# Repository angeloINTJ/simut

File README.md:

<p align="center">
  <picture>
    <source media="(prefers-color-scheme: dark)" srcset="docs/images/logo-wordmark-dark.svg">
    <source media="(prefers-color-scheme: light)" srcset="docs/images/logo-wordmark.svg">
    
  </picture>
</p>

# SIMUT — Sistema Integrado de Monitoramento Universal e Telemetria

> In English, *Integrated Universal Monitoring and Telemetry System*. The name is Portuguese, and so is the acronym: it is not translated.

> Offline-first monitoring and telemetry for the Raspberry Pi Pico W and Pico 2 W, on sixteen universal sensor slots

[English](README.md) | [Português](README.pt-BR.md) | [Español](README.es-ES.md)

## Overview

SIMUT is monitoring and telemetry firmware for the **Raspberry Pi Pico W** and the **Pico 2 W**. It reads up to 16 sensors on universal slots — temperature, humidity and pressure today, through its DS18B20, DHT22 and BMP280/BME280 drivers — records them on the device, raises alarms, and keeps working with or without a network. One source tree builds three published devices:

- a **touch-panel monitor** (320×240 TFT);
- a **character-LCD monitor** (16×2, the *alpha*);
- a **battery logger** that hibernates between readings (the *Air*, experimental).

They share one core:
- binary on-device history and per-channel alarms;
- 32 user accounts with 13 permission bits;
- an embedded web interface;
- telemetry over HTTP(S) or MQTT(S), with a separate line for alarms;
- Home Assistant MQTT Discovery, a Prometheus `/metrics` endpoint and remote syslog (RFC 5424);
- over-the-air updates and a serial console.

**Universal is the direction, not a feature.** A slot has no fixed quantity: a sensor type is a driver under `src/sensors/` and an entry in the type table, a new quantity is a row in the channel table (four of the eight it has room for are used), and the dashboard, the history, the alarms, the calibration and the telemetry read the driver's metadata instead of special-casing a part ([adding a sensor](docs/adding-a-new-sensor.md)). Three drivers ship today, and the table already has a row for luminosity that none of them fills. The project's direction is more drivers, contributed one at a time, and slots that actuate — relays, valves, signals — as well as read. No image drives an output yet: an alarm is a sound, a screen and a message to your server.

## Project status

| | |
|---|---|
| **Current release** | **v2.14.0** (2026-11-05); the [changelog](CHANGELOG.md) says what each version changed. SIMUT left beta with v2.7.0, on measurements: an 8.18 h soak with 0 reboots, and 6 of 6 over-the-air updates with nothing lost. |
| **Published images** | Four images, each as `.uf2` and `.bin`. For the Pico W: `release` (TFT touch panel), `alpha` (16×2 LCD with a Bluetooth console) and `air` (headless battery logger). For the Pico 2 W (RP2350): `releasetwo`, the release, whose `.uf2` carries its partition table and whose `.bin` boots on trial. The pt-BR and es-ES language packs and an OTA manifest ship alongside. An image with a different set of features comes from the [build configurator](https://angelointj.github.io/simut/configurador/), and CI builds it from `main`, for the Pico 2 W too. |
| **Maturity** | <ul><li>`release`: **stable**.</li><li>`alpha`: published and bench-tested, its 16×2 LCD included since 2026-09-26.</li><li>`air`: **experimental**. Its one long soak failed: a sleep in cycle 119 never woke (F28). A watchdog across the wake now mitigates it; the root cause is not confirmed.</li><li>`releasetwo`: **new** in v2.11.0, bench-tested on one Pico 2 W (RP2350 A2). It updates over the air into its other slot, on trial, and goes back by itself when the update does not keep itself.</li></ul> |
| **Tests** | Every pull request runs 883 host test cases in 11 suites, 60 s of fuzzing and static analysis, and builds all eleven firmware images from a cold cache. Behaviour on real hardware is verified on a bench — see [Verification on hardware](docs/VERIFICATION.md). |

**Known limitations.** Each one is documented where it applies.
- **Updates.** On the Pico W, an update over the air reformats the filesystem:
  - Wi-Fi, accounts and sensor slots are carried across. History, calibration files and language packs are not, so the web page downloads a backup before it starts, and restoring it brings them back.
  - On the Pico W there is one firmware slot and no rollback. A bad flash is recovered with BOOTSEL and a USB cable. The Pico 2 W has two slots: an update goes into the other slot, leaves the filesystem alone and boots on trial, and the image it replaced comes back by itself if the new one does not keep itself ([What an update destroys](docs/MANUAL.md#what-an-update-destroys), [Rollback](docs/MANUAL.md#rollback)).
  - Since v2.9.0, only an image the project signed installs over the air: a release `.bin`, or a build from the configurator. A build of your own goes over USB.
- **Unexplained resets.** A watchdog reset (`ctx=209` or `ctx=455`) appeared three times on the test image on 20–21 September and not since; the one caught with its context had Core 0 in the console (`ctx=209`). Both cores are now instrumented to explain the next one. A `ctx=455` (empty trace) on the first boot after `picotool load -x` is not this: that reboot goes through the watchdog, and the record appeared after 11 of 11 such flashes and after none of 7 hardware resets (2026-09-30).
- **Idle connections.** During the v2.7.0 soak, 7.1 % of responses on an idle keep-alive connection arrived cut short. The device drops a stream it cannot send for 4 s.
- **Chunked replies.** Read in a tight loop, 0.15–0.6 % of `/api/status` replies arrive with their chunked framing broken ([#189](https://github.com/angeloINTJ/simut/issues/189)). The device does not restart and the next request works; the page misses one update.
- **Not a certified instrument.** SIMUT is not a certified metrological instrument. Validate it against your own reference before relying on it for regulated storage.

## Why SIMUT?

| Need | DIY Arduino sketch | ESPHome / Tasmota | **SIMUT** |
|------|:---:|:---:|:---:|
| Standalone with display | Manual coding | No TFT support | Built-in touch UI, or a 16×2 LCD |
| Regulated environments | No audit trail | No user RBAC | 32 accounts, per-account panel PIN, a persistent event log and remote syslog |
| Cold chain (probes down to −50 °C) | Basic readings | Basic monitoring | Calibrated multi-sensor, maintenance windows |
| Offline operation | Yes | Often cloud-dependent | Full local web + display |
| OTA updates | Manual reflash | OTA | Signed OTA + backup/restore |
| Security | None | Basic | HMAC-SHA256, 13-bit RBAC, lockouts, optional HTTPS |
| Home Assistant | Manual setup | Native | MQTT Discovery (opt-in) |
| Prometheus metrics | None | Built-in | `/metrics` endpoint |
| Remote audit log | None | Add-on | Syslog (RFC 5424 / UDP) |

**SIMUT is for you if:** you need a standalone, secure, auditable monitoring system that works with or without internet — today typical in laboratories, pharmacies, blood banks, vaccine storage and food cold chains, and wherever a sensor with a driver needs a screen, a history and an alarm.

**ESPHome/Tasmota may be better if:** you don't need a local display and prefer YAML configuration over a built-in web UI. (If what kept you there was Home Assistant: SIMUT speaks MQTT Discovery.)

## Architecture

<picture>
  <source media="(prefers-color-scheme: dark)" srcset="docs/images/architecture-dark.svg">
  <source media="(prefers-color-scheme: light)" srcset="docs/images/architecture.svg">
  
</picture>

Core 0 runs everything but the display, in one cooperative loop, and is the only core that writes the flash; Core 1 runs only the display, the touch panel or the LCD. The rules between the two are in [docs/CONCURRENCY.md](docs/CONCURRENCY.md). The figure is drawn from the source by `tools/readme_diagram.py`, and CI checks that it still matches the code.

## Screenshots

| TFT dashboard (Pico W) | TFT history graph (Pico W) | Web dashboard | Early alpha |
|:---:|:---:|:---:|:---:|
|  |  |  |  |

> Every screen of the Pico W's original panel, captured off the real panel framebuffer: [docs/images/screens/screens.md](docs/images/screens/screens.md).
>
> The **early alpha** video shows the first TFT + touch prototype — the UI has been redesigned since.

## Hardware

| Component | Specification |
|-----------|---------------|
| MCU | Raspberry Pi Pico W (RP2040) or Pico 2 W (RP2350), both dual-core. The SIMUT Wire, a plain Pico with an ENC28J60 Ethernet module in place of the radio (`pico_wire`, `pico_wiretft`), is built by CI and runs on the bench; it is not published |
| Display | `release`: ILI9341 320×240 TFT (SPI, DMA-driven), in the Ângulo look on the Pico 2 W (v2.12.0 and earlier drew the original panel there) and the original look on the Pico W · `alpha`: HD44780 16×2 character LCD (4-bit) · `air`: none |
| Touch | XPT2046 resistive touchscreen (`release`) |
| Sensors | **16 universal slots on GP0–GP15** — any mix of DS18B20 (1-Wire), DHT22 and BMP280/BME280. A BMx280 is I²C and takes two pins; two of them can share a pair (0x76/0x77). A new sensor type is a driver; a new quantity, a row in the channel table ([adding a sensor](docs/adding-a-new-sensor.md)) |
| Buzzer | Passive piezo (PIO-driven) — not on the Air |
| Storage | 2 MB internal flash (1 MB firmware slot + 1 MB LittleFS) |

See the **[wiring guide](docs/WIRING.md)** for the complete pinout and connection diagrams.

> **SIMUT PCB — layout available for download** — the KiCad board design (`.kicad_pcb`, `.kicad_sch`) lives in [`PCB_test/`](PCB_test/), and the ready-to-fab package (Gerbers + PTH/NPTH drills, no paste layers) is published as a public release: **[simut-pcb-v1.1 — `simut_pcb_fabrication.zip`](https://github.com/angeloINTJ/simut/releases/tag/simut-pcb-v1.1)**.

## Features

- **Sensing and alarms** — 16 universal sensor slots assigned at runtime, three drivers today (DS18B20, DHT22, BMP280/BME280) in a channel table open to more, calibration curves, per-channel limits, a fault alarm and maintenance windows.
- **Touch panel** (`release`) — dashboard, history graphs and calendar, and identity at the glass: an account, then its PIN. The Pico 2 W release draws it in the Ângulo look; the Pico W release keeps the original panel. v2.12.0 and earlier drew the original panel on the Pico 2 W.
- **Character LCD** (`alpha`) — every slot in turn, the setup access point and a Bluetooth console; since v2.14.0 the web dashboard draws the glass itself, captured once or live (`GET /api/lcd`).
- **Web interface** — 11 pages, a live panel mirror, history graphs and CSV export in the browser.
- **HTTP API** — 63 routes. Each one is either gated by a permission or public by design, and CI checks it. The images with the Ângulo panel add `GET /api/ui`, gated.
- **Telemetry** — HTTP, HTTPS, MQTT and MQTTS, batched by quantity, and a second, acknowledged line for alarms; Home Assistant, Prometheus and syslog.
- **Network and time** — Wi-Fi that reconnects itself, a setup access point opened on request, and NTP with a provisional clock until it syncs.
- **Storage** — the V5 binary history (about 116 days in 1 MB), a configuration with CRC32 and a `.bak`, and an event log with 170 event codes.
- **Security** — 32 accounts, 13 permission bits, salted HMAC-SHA256, lockouts and optional HTTPS.
- **Updates** — signed over-the-air updates from the web page, and backup and restore of the whole filesystem.
- **SIMUT Air** (experimental) — a battery logger that hibernates between readings.
- **Languages** — English built in; pt-BR and es-ES as language packs.

Every feature in detail, and which ones a custom build can leave out: **[docs/FEATURES.md](docs/FEATURES.md)**.

## Quick start

### Prerequisites
- [PlatformIO](https://platformio.org/) (Core 6.x or later)
- `pip install zopfli` — optional; the web pages compress 2,888 B smaller with it, and the flash budgets are measured with it
- Raspberry Pi Pico W
- No local toolchain? `docker compose run build` builds in a container — the path [CONTRIBUTING.md](CONTRIBUTING.md) recommends for new contributors

### Build and flash

```bash
# Clone the repository
git clone https://github.com/angeloINTJ/simut.git
cd simut

# Build firmware
pio run -e pico_w_release

# Flash to Pico W (auto-reset via 1200 bps touch; BOOTSEL works too)
pio run -e pico_w_release -t upload

# First flash only: upload LittleFS data (language packs, themes, favicon).
# Warning: uploadfs reformats the LittleFS partition — on a device already in
# service it destroys history, config and calibration. Never run it again
# after the device has data; language packs can be uploaded later from the
# web file manager instead. It copies both language packs, and the device
# loads the first alphabetically (es-ES): delete the one you do not want.
pio run -e pico_w_release -t uploadfs
```

Prefer not to build? Every [release](https://github.com/angeloINTJ/simut/releases/latest) ships `simut_vX.Y.Z_release.uf2`, `_alpha.uf2` and `_air.uf2` for the Pico W and, since v2.11.0, `_releasetwo.uf2` for the Pico 2 W (drag-and-drop with BOOTSEL held), the matching `.bin` for over-the-air updates, and the pt-BR and es-ES language packs. An image with a different set of features comes from the [build configurator](https://angelointj.github.io/simut/configurador/).

### First boot
1. **Capture the admin password.** A factory-fresh unit prints a random 8-character admin password **once on the USB serial console** (115200 baud). It is never stored in plain text. If you miss it, `system admin reset confirm` over USB prints a new one.
2. **Join it to your network.** The setup access point opens when you ask for it: type `ap` on the console (on the Air, after `enable`), or use Settings → 8 on the touch panel. From v2.7.1 to v2.8.0, a unit with no network configured opened it by itself; it no longer does.
   - Join `<name>_SETUP` (`simut_SETUP` from the factory). It is WPA2, and its per-device key is in the reply to `ap`, on the USB console and on the TFT's boot terminal.
   - The portal opens at `http://192.168.4.1`.
   - The device keeps measuring while the access point is up; only telemetry and syslog wait for the network. v2.7.1 to v2.8.0 read no sensors, checked no alarms and recorded no history while it was up.

   Without a screen, you can use the console instead: `system ssid <name>`, `system pass <secret>`, then `reload confirm`. The console stops at the first space, so a network name or password with a space has to go through the web page.

   With no network configured, the unit asks for the date and time at the end of the boot, because without a network there is no NTP: the touch panel opens a date-and-time screen (**SKIP** leaves it, and Settings → 4 sets the clock later), and every image prints `No network, provisional clock: conf time YYYY-MM-DD HH:MM:SS` on the console. That command works on every image's console, over USB or Bluetooth: on the alpha and the Air, which have no panel, it is how the question is answered. The web page's **Date & Time** section sets the clock too.
3. **Open the web interface** at the address the device got — on the `release` image also `http://simut.local` — and log in as `admin` with the password from step 1. You will be asked to choose a new one.
4. **Add sensors** in **Config → Sensors & GPIO**, or let *Scan for probes* find them.
5. **On the touch panel**, Settings asks for an account and its PIN. The factory admin PIN is `1234`, and it must be changed on first use.

## Project structure

```
simut/
├── src/                    # Firmware source (C++17)
│   ├── main.cpp            # Entry point
│   ├── AppManager*         # Application state machine, boot, alarms, Air cycle
│   ├── DisplayManager*     # TFT panel and alpha LCD (Core 1), touch, themes
│   ├── WebManager*         # Web server, HTTP API, sessions, OTA, TLS
│   ├── StorageManager*     # LittleFS, config, accounts, history files
│   ├── SensorManager*      # The sensor host: driver registry, read loop, error hysteresis
│   ├── NetworkManager*     # Wi-Fi, reconnect ladder, setup AP, mDNS, NTP
│   ├── TelemetryManager*   # HTTP(S)/MQTT(S) telemetry and the alarm line
│   ├── CommandManager*     # Serial and Bluetooth console
│   ├── LogManager*         # Event log and crash forensics
│   ├── HistoryV5.*         # V5 history codec
│   ├── air/                # SIMUT Air configuration
│   ├── display/            # Keypads, fonts and labels shared by the displays
│   ├── net/                # The network as a driver: CYW43 Wi-Fi, ENC28J60 (the Wire)
│   ├── sensors/            # Sensor drivers (DS18B20, DHT22, BMx280), channel table, calibration curves
│   ├── ota/                # Update staging, validation and applier
│   ├── ui/                 # The panel's UI drivers: original and Ângulo
│   └── SystemDefs*.h       # System constants and limits
├── data/                   # LittleFS assets (language packs, themes, favicon)
├── PCB_test/               # KiCad PCB design + Gerber/DRL fabrication files
├── test/                   # Native unit tests (Unity), eleven suites
├── tools/                  # Build gates, bench suites, PicoHand, release scripts, theme editor
├── docs/                   # Documentation + GitHub Pages site
├── WebUI.h                 # Web UI source (gzipped into src/WebUI_GZ.h at build)
├── AGENTS.md               # Bench manual: flashing, the Air, measuring (Portuguese)
└── platformio.ini          # Build configuration
```

## Building

### Environments

| Environment | Purpose | Published |
|-------------|---------|:---:|
| `pico_w_release` | Production image for the TFT panel: emergency console, HTTPS server, mDNS | `…_release` |
| `pico_w_alpha` | 16×2 character LCD (HD44780), no touch; emergency console + Bluetooth console | `…_alpha` |
| `pico_w_air` | **Experimental** — SIMUT Air: headless, no buzzer, hibernation cycle (M0 awake / M1 wake-read-send-sleep); full console + Bluetooth. See §17 of the [user manual](docs/MANUAL.md) | `…_air` |
| `pico_w_test` | Bench image: the full console for the test suites; no HTTPS, no mDNS | — |
| `pico_w_test_https` | `pico_w_test` plus the HTTPS server, for TLS validation; three of its pages are served from LittleFS to fit | — |
| `pico_w_asserts` | Release + concurrency assertions | — |
| `pico2_w_release` | The release for the Pico 2 W (RP2350): it boots from slot A or B of a partition table and updates over the air into the other, on trial ([OTA_AB_RP2350.md](docs/analysis/OTA_AB_RP2350.md)). Its `.uf2` is a factory image, with the partition table. It draws the touch panel in the Ângulo look (v2.12.0 and earlier drew the original panel) | `…_releasetwo` |
| `pico2_w_original` | The Pico 2 W with the original panel, the look it carried up to v2.12.0; built by CI, not published, not a required check | — |
| `pico_wire` | The SIMUT Wire: a plain Pico with no radio, an ENC28J60 Ethernet module (`src/net/`) and the 16×2 LCD; on the bench since 2026-10-12, built by CI, not published | — |
| `pico_wiretft` | The Wire with the TFT panel and touch in place of the LCD, in the original look | — |
| `pico_wiretft_angulo` | `pico_wiretft` drawn by the Ângulo UI driver (`src/ui/angulo/`) | — |
| eleven `native*` envs | Host-side unit tests — see [Testing](#testing) | — |

> **Security note for `pico_w_alpha` and `pico_w_air`:** both compile the
> Bluetooth SPP console in (`SIMUT_BLUETOOTH=1`), so on those two images it is
> live attack surface. It is authenticated by the **admin web password**, with
> an exponential lockout that survives a reconnect, and a discovery window that
> closes 5 minutes after boot. Recovery commands are restricted to USB.
>
> The setup access point is WPA2 on every image, with a per-device key shown on
> the console and, where there is one, on the display. See [SECURITY.md](SECURITY.md) §2 and §8.

> There is no debug environment. `pico_w_debug` was removed in v2.4.1 after never once linking: at `-Og` the image overflowed the 1020 KB app slot by ~100 KB. Flash is tight. The release image uses 98.2 % of the 1,044,480 B program slot (`tools/flash_budget.json` keeps the measured value), and CI checks every `.bin`, with its 241 B signature, against the 1,040,384 B over-the-air ceiling. A GDB target would have to be built by cutting features. For the concurrency tripwire on hardware, use `pico_w_asserts`.

### Build flags
- `-Os` — optimize for size
- `-Wall -Wextra`, and `-Werror` on `src/` (third-party libraries are not held to it)
- `-specs=nano.specs` — newlib-nano for smaller binary
- `-DNDEBUG` on every image
- LTO is disabled (toolchain limitation with earlephilhower Arduino-Pico)
- The framework is pinned to arduino-pico 5.6.1 and patched by `tools/arduino_pico_overrides/patch.sh`

## Configuration

### Console (CLI)
A serial console is available over USB (115200 baud), and over Bluetooth SPP on the alpha and the Air.

- **The emergency console** runs on the `release` and `alpha` images. Its 15 commands:
  - `show net status`, `show system info`, `show system log`
  - `debug on|off`
  - `system admin reset`, `system format`, `system factory`, `system https off`
  - `system ssid <name>`, `system pass <secret>`, `system cors <origin|off>`
  - `ap`, `time <date> <time>`, `reload`, `help`

  Destructive commands ask for `confirm`, and the four recoveries (`system factory`, `system format`, `system admin reset`, `system https off`) are refused over Bluetooth.
- **The full Cisco-style console** (`enable` / `configure terminal`) runs on the `air` image and the `pico_w_test` bench images — see the [CLI manual](docs/CLI-Manual.md) (in Portuguese). The Air adds `air status | hibernate | stop | idle <sec> | charger <gpio|off>`.

**Where configuration happens:**
- **The web interface** is the day-to-day tool.
- **The touch panel** covers what an operator needs at the device: themes, alarms, sounds, language, their own PIN, users, the PIN policy, touch calibration, display offset, status, the setup access point and the date and time.

### Web API
The device exposes a REST API at `http://<device-ip>/api/`:
- **63 routes** — 53 gated by a permission, 10 public by design, 0 ungated, checked by `tools/check_authz.py` in CI;
- the images with the Ângulo panel also serve `GET /api/ui`, gated by `PERM_SYS_CONFIG` and counted apart, outside the 62;
- the route table is in the [user manual](docs/MANUAL.md);
- [docs/AUTHORIZATION.md](docs/AUTHORIZATION.md) maps each route to its permission;
- [docs/API_POST.md](docs/API_POST.md) documents the POST bodies.

## Testing

### Host tests

```bash
pio test -e native             # validators, telemetry cursor, labels, parsers, language packs, the License and update screens, the Settings menu, the password check, the web session, the alpha LCD's screens and the shadow of its glass (450 cases)
pio test -e native_history_v5  # V5 history codec (62)
pio test -e native_cli         # CLI parser (43)
pio test -e native_lan         # CLI parser, pack help, Settings menu, log codes and the alpha LCD's cable cells of a wired build (19)
pio test -e native_logpolicy   # edge-triggered log persistence, autopsy bands, touch wake (59)
pio test -e native_alarmqueue  # alarm telemetry queue (54)
pio test -e native_network     # Wi-Fi reconnect state machine (54)
pio test -e native_wired       # wired network state machine, against a fake ENC28J60 (19)
pio test -e native_air         # SIMUT Air persistent config (17)
pio test -e native_sensors     # sensor type table, scan JSON, the real BMx280 scan (23)
pio test -e native_otasig      # OTA image signature check, the backup restore, and the RP2350's slot writer and update on trial (83)

# V5 codec reference checks (Python vs C++, 20k random cases)
python3 tools/check_history_v5_parity.py --cases 20000
python3 tools/history_v5.py --selftest --trials 200000
```

### Continuous integration

Every push and pull request to `main` runs four jobs:
- **gates** — the host suites plus these checks:
  - secret scan, log-code tables, authorization matrix;
  - licence consistency, filesystem guard, Air consistency;
  - history day-merge tests.
- **firmware** — all eleven images, built from a cold cache:
  - each is checked against its flash budget and the over-the-air ceiling;
  - the build itself enforces `-Werror` and the web UI, CLI help, log-code, channel-table and language-pack gates.
- **fuzz** — 60 s of libFuzzer against the web-API validators, with contract oracles.
- **static analysis** — cppcheck, at a pinned version.

`main` is protected: nine of these checks must pass before anything merges, every job except the `pico_w_test_https`, `pico_wire`, `pico_wiretft`, `pico_wiretft_angulo` and `pico2_w_original` images.

### Verification on hardware

Behaviour is checked on a bench: a Pico 2 W with the TFT panel and touch, and a Pico W, the *PicoHand*, that works the target's RESET and BOOTSEL lines. Every measurement, dated, with its numbers: **[docs/VERIFICATION.md](docs/VERIFICATION.md)**.

## Documentation

| Document | Description |
|----------|-------------|
| [User manual](docs/MANUAL.md) | Hardware setup, display/web/console guide, OTA, API reference, troubleshooting — kept current |
| [Manual do usuário (pt-BR)](docs/MANUAL.pt-BR.md) | The same manual, in Portuguese |
| [Complete manual (pt-BR)](docs/MANUAL.pt-BR.html) | The full product manual in Portuguese, updated for v2.14.0: installation, configuration, daily use and server integration, with 245 figures, screens and diagrams; the 10 still pending (2026-11-06) are marked where they belong |
| [Wiring guide](docs/WIRING.md) | Complete pinout and connection diagrams |
| [Over-the-air updates](docs/OTA_USAGE.md) | Updating from the web page, and what survives it |
| [Recovery guide](docs/RECOVERY.md) | Brick recovery — BOOTSEL, picotool, 1200 bps reset |
| [CLI manual](docs/CLI-Manual.md) | Full console reference, the Air's included (in Portuguese) |
| [Authorization matrix](docs/AUTHORIZATION.md) | Every HTTP route and the permission it requires |
| [Security policy](SECURITY.md) | Threat model, credential handling, incident response |
| [Features](docs/FEATURES.md) | Every feature in detail |
| [Verification on hardware](docs/VERIFICATION.md) | What has been measured on the bench, dated |
| [Documentation index](docs/README.md) | Which documents are kept current and which are snapshots |
| [Changelog](CHANGELOG.md) | Version history and feature changes |

## How SIMUT is developed

Most changes are written by an AI coding agent (Claude Code) in sessions the maintainer directs: from 1 September to 2 October 2026, 275 of the 371 commits on `main` carried a `Co-Authored-By: Claude` line. The instructions those sessions follow are [CLAUDE.md](CLAUDE.md) and [AGENTS.md](AGENTS.md) (in Portuguese). The rules are the same for every change, whoever typed it:
- it reaches `main` only through a pull request, after nine required checks pass: the eleven host test suites, also under AddressSanitizer and UBSan, 60 s of fuzzing, static analysis, and six of the eleven firmware images built from a cold cache;
- the tests come first: a fix carries a reproduction that fails before it and passes after, and a refactor shows that the behaviour did not change;
- a claim about bytes, speed or a fix carries its measurement, and what was not checked on hardware says so;
- product decisions, and the decision to merge, are the maintainer's.

## Contributing

Contributions are welcome. Read [CONTRIBUTING.md](CONTRIBUTING.md) for the development setup, the code conventions and the pull request process.

All contributors must follow the [Code of Conduct](CODE_OF_CONDUCT.md).

## Support

- **Bug reports:** [GitHub Issues](https://github.com/angeloINTJ/simut/issues/new?template=bug_report.md)
- **Feature requests:** [GitHub Issues](https://github.com/angeloINTJ/simut/issues/new?template=feature_request.md)
- **Security vulnerabilities:** See [SECURITY.md](SECURITY.md) — do not open a public issue
- **Questions:** Open a discussion or issue

## Contributors

Thanks to everyone who has contributed:

<!-- ALL-CONTRIBUTORS-LIST:START - Do not remove or modify this section -->
<!-- prettier-ignore-start -->
<!-- markdownlint-disable -->
<table>
  <tbody>
    <tr>
      <td align="center" valign="top" width="14.28%"><a href="https://github.com/angeloINTJ"><br /><sub><b>Ângelo Moisés Alves</b></sub></a><br /><a href="https://github.com/angeloINTJ/simut/commits?author=angeloINTJ" title="Code">💻</a> <a href="https://github.com/angeloINTJ/simut/commits?author=angeloINTJ" title="Documentation">📖</a> <a href="#design-angeloINTJ" title="Design">🎨</a> <a href="#hardware-angeloINTJ" title="Hardware">🔌</a> <a href="#security-angeloINTJ" title="Security">🛡️</a> <a href="#maintenance-angeloINTJ" title="Maintenance">🚧</a></td>
      <td align="center" valign="top" width="14.28%"><a href="https://github.com/LorenzoLongaretto"><br /><sub><b>Lorenzo Longaretto</b></sub></a><br /><a href="https://github.com/angeloINTJ/simut/commits?author=LorenzoLongaretto" title="Tests">🧪</a> <a href="https://github.com/angeloINTJ/simut/commits?author=LorenzoLongaretto" title="Code">💻</a></td>
      <td align="center" valign="top" width="14.28%"><a href="https://github.com/JohnMartin0301"><br /><sub><b>John Martin</b></sub></a><br /><a href="#infra-JohnMartin0301" title="Infrastructure">🚇</a> <a href="https://github.com/angeloINTJ/simut/commits?author=JohnMartin0301" title="Code">💻</a></td>
      <td align="center" valign="top" width="14.28%"><a href="https://github.com/f-p-0"><br /><sub><b>f p</b></sub></a><br /><a href="https://github.com/angeloINTJ/simut/commits?author=f-p-0" title="Documentation">📖</a></td>
      <td align="center" valign="top" width="14.28%"><a href="https://github.com/drmikecrypto"><br /><sub><b>Mike</b></sub></a><br /><a href="https://github.com/angeloINTJ/simut/commits?author=drmikecrypto" title="Code">💻</a> <a href="https://github.com/angeloINTJ/simut/commits?author=drmikecrypto" title="Tests">🧪</a> <a href="https://github.com/angeloINTJ/simut/commits?author=drmikecrypto" title="Documentation">📖</a></td>
    </tr>
  </tbody>
</table>
<!-- markdownlint-restore -->
<!-- prettier-ignore-end -->
<!-- ALL-CONTRIBUTORS-LIST:END -->

This project follows the [all-contributors](https://allcontributors.org) specification.

## Powered by SIMUT

Is your product or project using SIMUT? Add this badge to your README, documentation, or product page:

```markdown

```

**Large version** (for presentations, posters, or product packaging):

```markdown

```

---

## License

MIT License — see [LICENSE](LICENSE) for details.

The firmware images also carry third-party software. [THIRD_PARTY_NOTICES.md](THIRD_PARTY_NOTICES.md)
names each component, its copyright holder, its licence and the images that carry it, and
[LICENSES/](LICENSES) holds the licence texts. The device shows the same list on its License
screen and on the `/license` page.

Copyright © 2026 Ângelo Moisés Alves

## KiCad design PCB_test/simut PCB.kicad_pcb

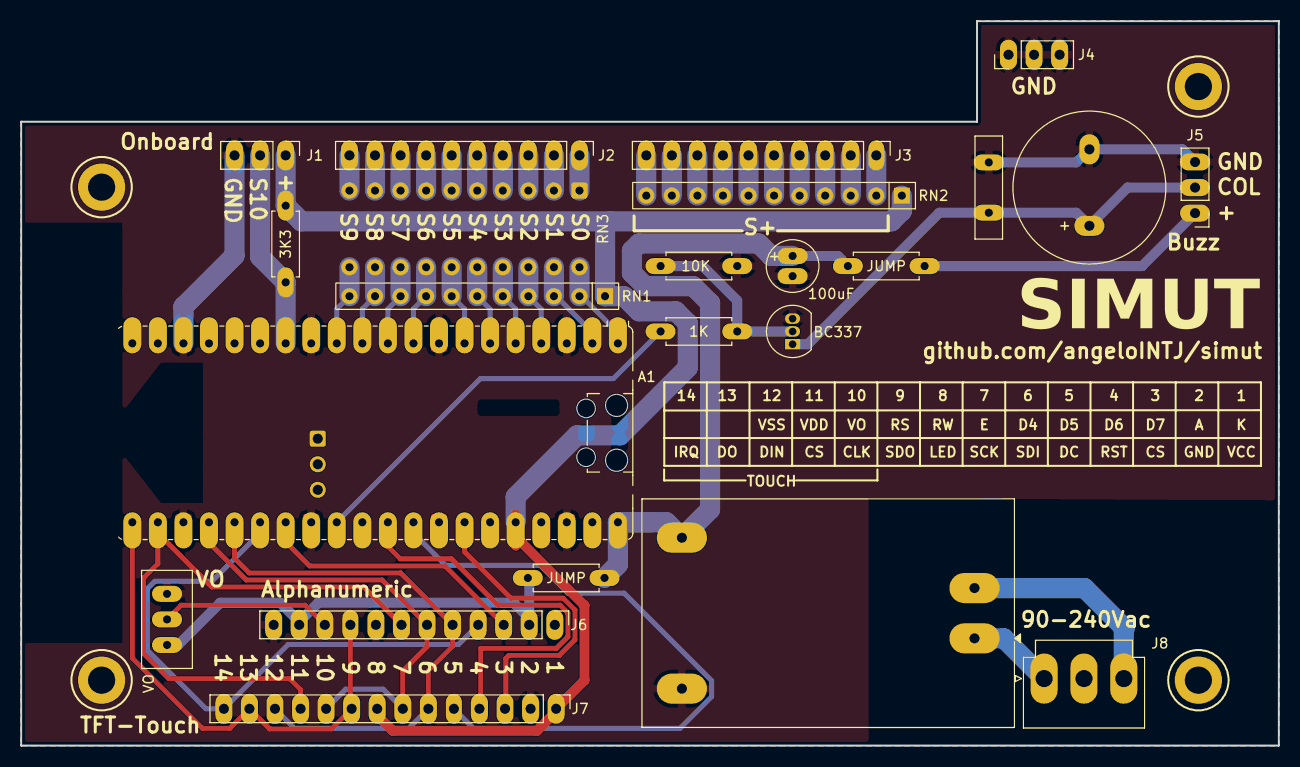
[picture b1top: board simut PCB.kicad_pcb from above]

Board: 2 copper layers, 125.0 x 72.0 mm, 23 parts (0 on the bottom side), 51 nets.

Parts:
100uF: C_Small_US; C_Radial_D5.0mm_H11.0mm_P2.00mm
A1: RaspberryPi_Pico_W; RaspberryPi_Pico_W_SMD_HandSolder
BC337: BC337; TO-92_Inline
BZ1: Buzzer; Buzzer_15x7.5RM7.6
C2: C_Small; C_Disc_D10.0mm_W2.5mm_P5.00mm
J1, J4, J5: Conn_01x03; PinHeader_1x03_P2.54mm_Vertical
J2, J3: Conn_01x10; PinHeader_1x10_P2.54mm_Vertical
J6: Conn_01x12; PinHeader_1x12_P2.54mm_Vertical
J7: Conn_01x14; PinHeader_1x14_P2.54mm_Vertical
J8: Conn_01x03; JST_VH_B3P-VH-B_1x03_P3.96mm_Vertical
R31, R32, R33, R34, R35: R; R_Axial_DIN0207_L6.3mm_D2.5mm_P7.62mm_Horizontal
RN1, RN2: R_Network10; R_Array_SIP11
RN3: R_Pack10; DIP-20_W7.62mm
U2: HLK-PM01; Converter_ACDC_Hi-Link_HLK-PMxx
VO: R_Potentiometer_Trim; Potentiometer_Bourns_3296W_Vertical

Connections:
GND: 100uF.2, A1.3 (GND), A1.8 (GND), A1.13 (GND), A1.18 (GND), A1.23 (GND), A1.28 (GND), A1.38 (GND), BC337.3 (E), BZ1.2 (-), C2.2, J1.3, J4.1, J4.2, J4.3, J5.3, J6.1, J6.8, J6.12, J7.2, R34.2, U2.3 (-Vout), VO.3
unnamed: A1.1 (GPIO0), RN1.2 (R1), RN3.20 (R1.2)
unnamed: A1.2 (GPIO1), RN1.3 (R2), RN3.19 (R2.2)
unnamed: A1.4 (GPIO2), RN1.4 (R3), RN3.18 (R3.2)
unnamed: A1.5 (GPIO3), RN1.5 (R4), RN3.17 (R4.2)
unnamed: A1.6 (GPIO4), RN1.6 (R5), RN3.16 (R5.2)
unnamed: A1.7 (GPIO5), RN1.7 (R6), RN3.15 (R6.2)
unnamed: A1.9 (GPIO6), RN1.8 (R7), RN3.14 (R7.2)
unnamed: A1.10 (GPIO7), RN1.9 (R8), RN3.13 (R8.2)
unnamed: A1.11 (GPIO8), RN1.10 (R9), RN3.12 (R9.2)
unnamed: A1.12 (GPIO9), RN1.11 (R10), RN3.11 (R10.2)
unnamed: A1.14 (GPIO10), J1.2, R31.2
unnamed: A1.21 (GPIO16), J6.9, J7.9, J7.13
unnamed: A1.22 (GPIO17), J6.7, J7.11
unnamed: A1.24 (GPIO18), J6.6, J7.7, J7.10
unnamed: A1.25 (GPIO19), J6.5, J7.6, J7.12
unnamed: A1.26 (GPIO20), J6.4, J7.14
unnamed: A1.27 (GPIO21), J6.3
unnamed: A1.29 (GPIO22), R33.1
unnamed: A1.31 (GPIO26_ADC0), J7.4
unnamed: A1.32 (GPIO27_ADC1), J7.5
unnamed: A1.34 (GPIO28_ADC2), J7.3
unnamed: BC337.1 (C), BZ1.1 (+), C2.1, J5.2
unnamed: J2.1, RN3.1 (R1.1)
unnamed: J2.2, RN3.2 (R2.1)
unnamed: J2.3, RN3.3 (R3.1)
unnamed: J2.4, RN3.4 (R4.1)
unnamed: J2.5, RN3.5 (R5.1)
unnamed: J2.6, RN3.6 (R6.1)
unnamed: J2.7, RN3.7 (R7.1)
unnamed: J2.8, RN3.8 (R8.1)
unnamed: J2.9, RN3.9 (R9.1)
unnamed: J2.10, RN3.10 (R10.1)
unnamed: J3.1, RN2.2 (R1)
unnamed: J3.2, RN2.3 (R2)
unnamed: J3.3, RN2.4 (R3)
unnamed: J3.4, RN2.5 (R4)
unnamed: J3.5, RN2.6 (R5)
unnamed: J3.6, RN2.7 (R6)
unnamed: J3.7, RN2.8 (R7)
unnamed: J3.8, RN2.9 (R8)
unnamed: J3.9, RN2.10 (R9)
unnamed: J3.10, RN2.11 (R10)
unnamed: J6.10, VO.2
unnamed: J6.2, J6.11, R32.2, VO.1
unnamed: J5.1, R35.2
unnamed: J8.1, U2.1 (AC/L)
unnamed: J8.3, U2.2 (AC/N)
unnamed: BC337.2 (B), R33.2, R34.1
VCC: 100uF.1, A1.40 (VBUS), R32.1, R35.1, U2.4 (+Vout)
VDD: A1.36 (3V3), J1.1, J7.1, J7.8, R31.1, RN1.1 (common), RN2.1 (common)
